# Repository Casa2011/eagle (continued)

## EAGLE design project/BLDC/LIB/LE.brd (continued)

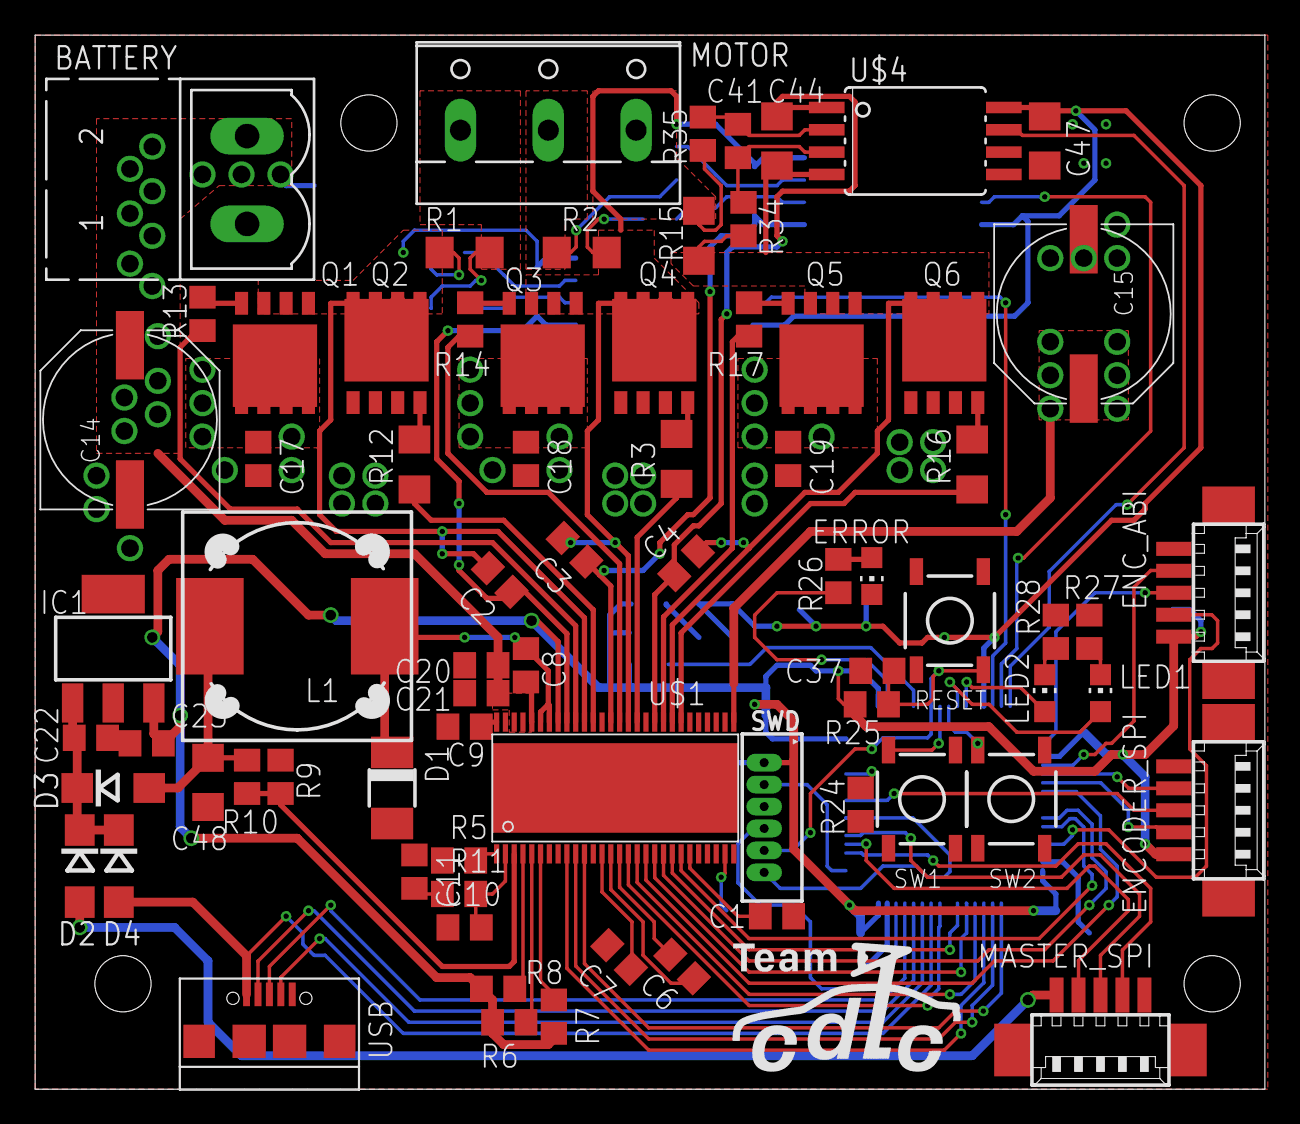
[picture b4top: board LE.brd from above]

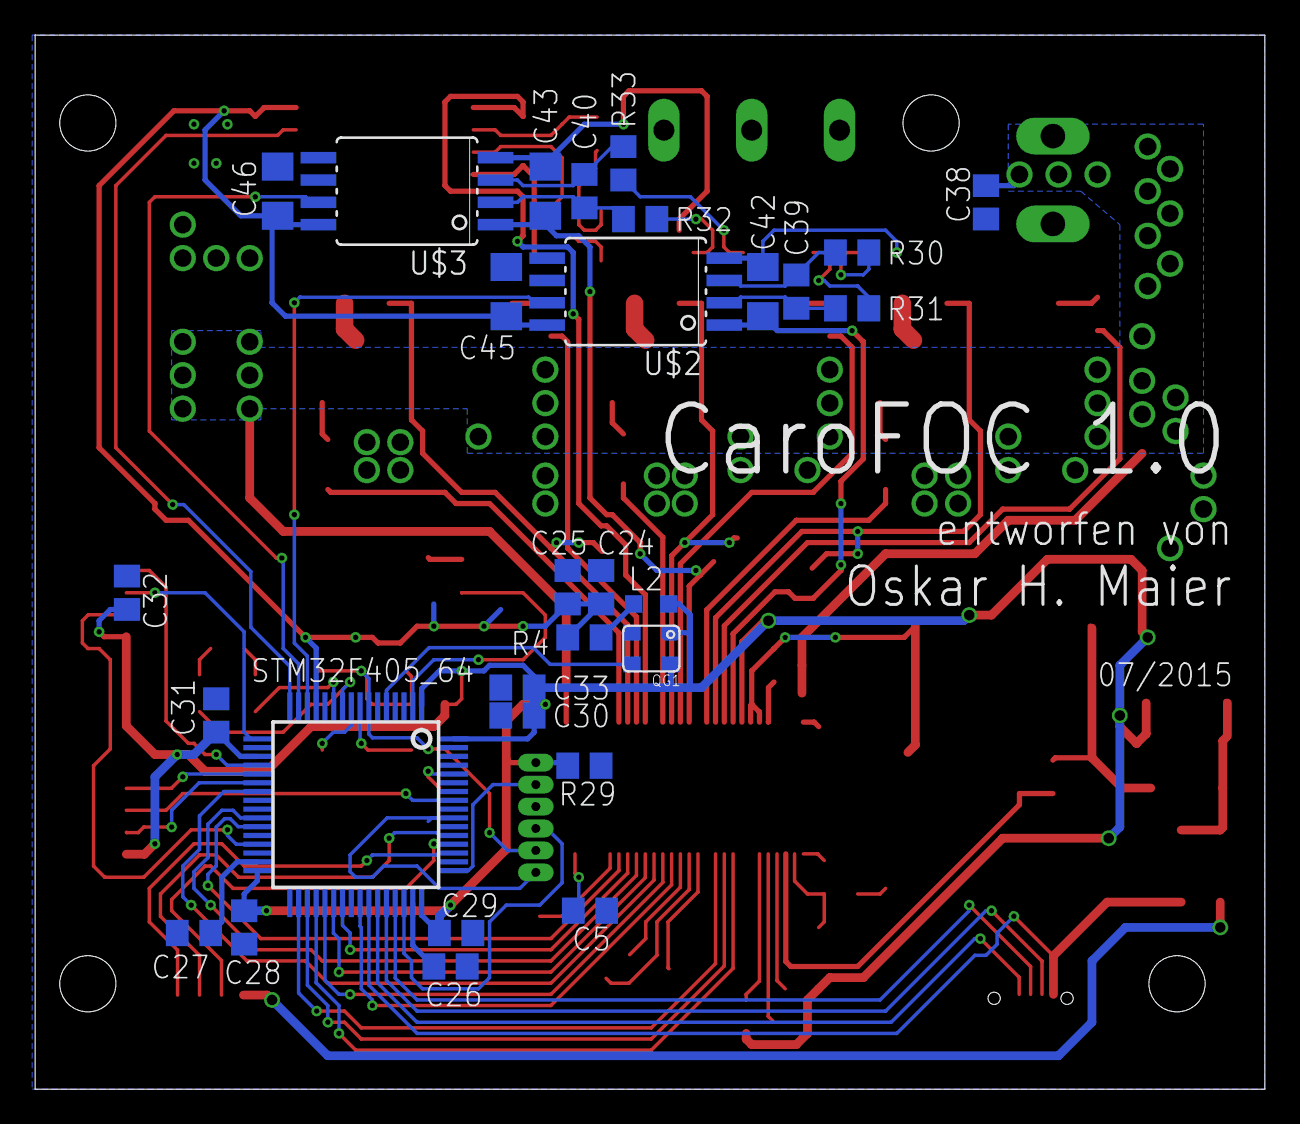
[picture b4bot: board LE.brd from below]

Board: 2 copper layers, 70.0 x 60.0 mm, 103 parts (29 on the bottom side), 92 nets.

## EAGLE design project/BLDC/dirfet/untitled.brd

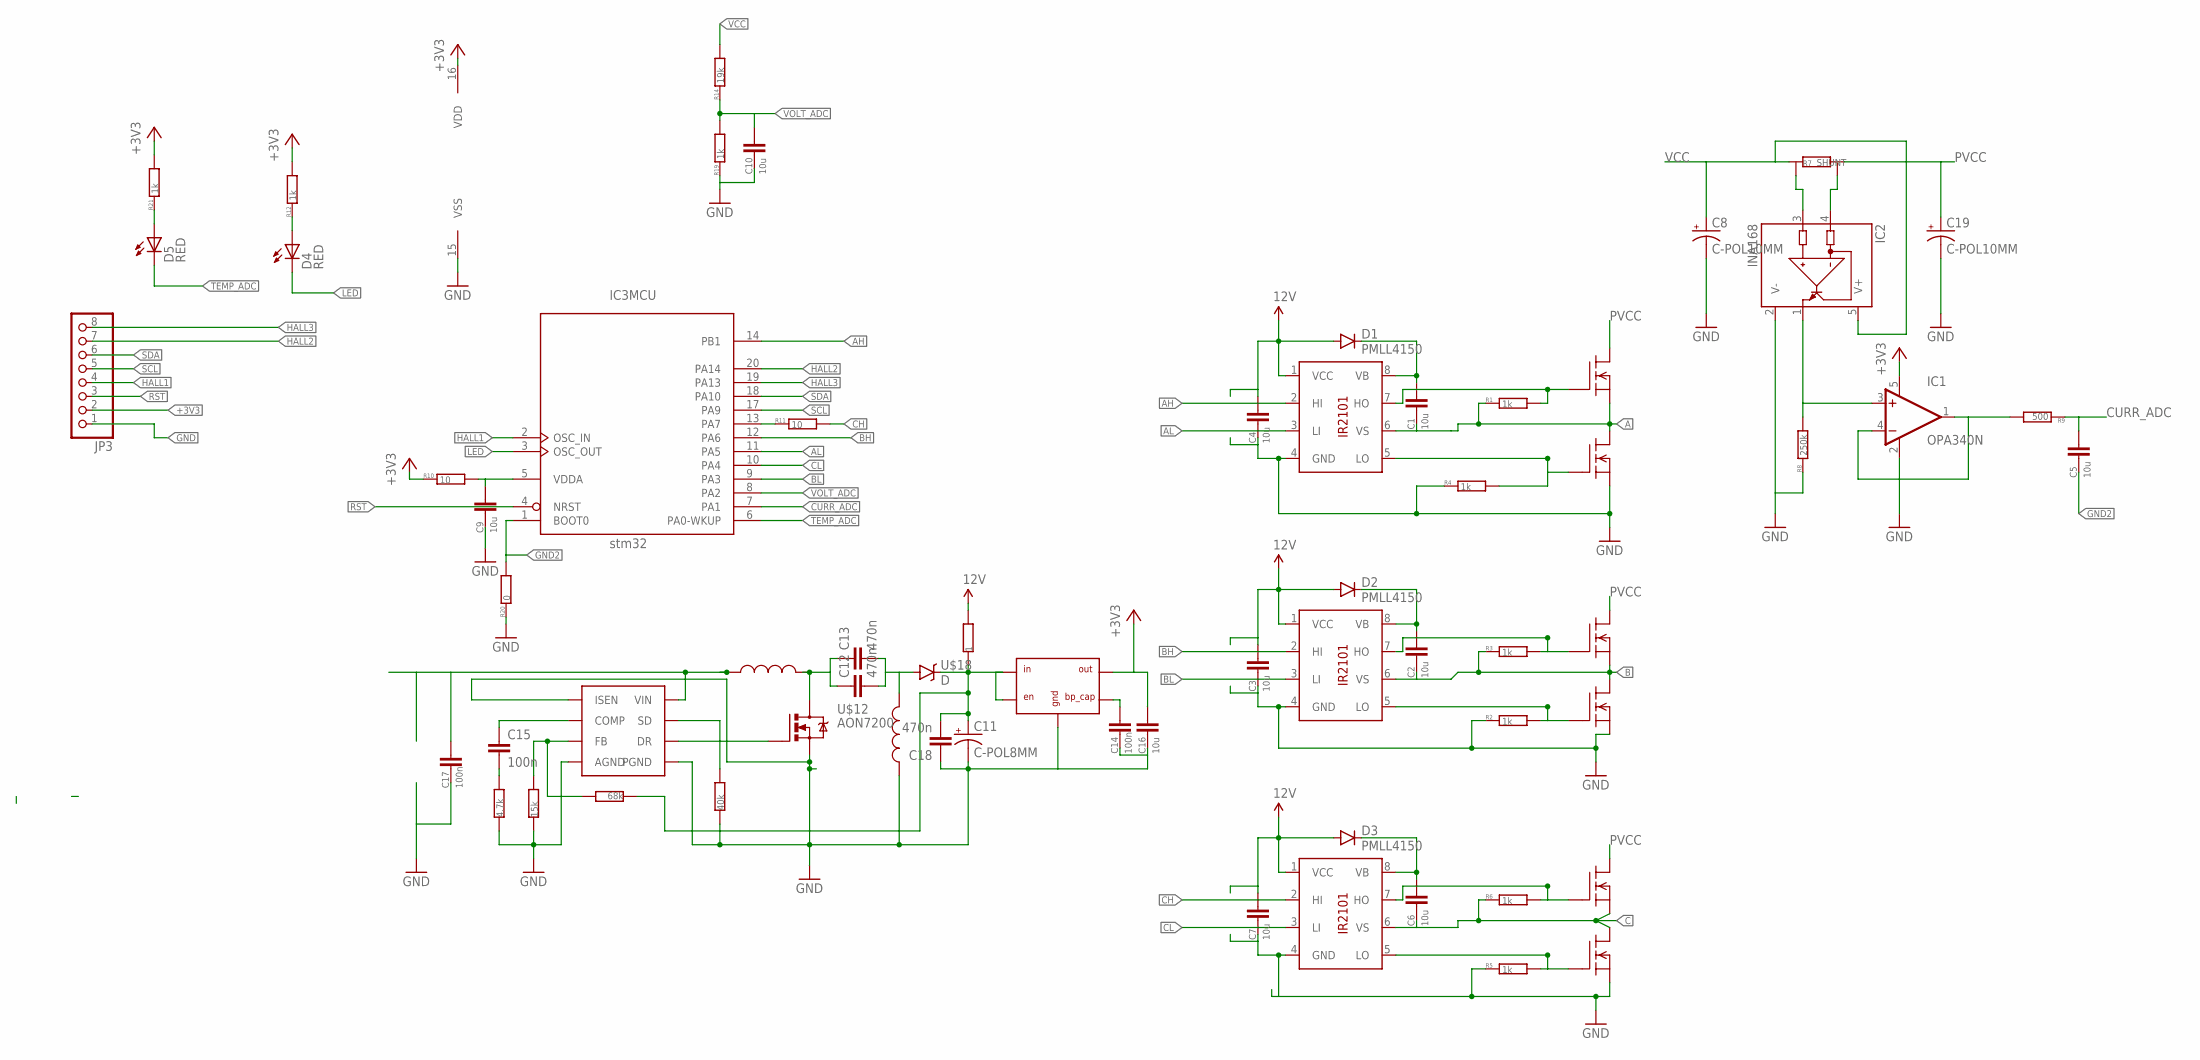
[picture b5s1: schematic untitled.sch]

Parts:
C1, C2, C3, C4, C6, C7, C9, C10, C16: 10u; C0805
C5: 10u; C0603
C8, C19: C-POL10MM; PCAP10
C11: C-POL8MM; PCAP8
C12, C13: 470n; C1206
C14: 100n; C0805
C15: 100n; C0603
C17: 100n; C1206
C18: 470n; C0805
D1, D2, D3: PMLL4150; SOD80C
D4, D5: RED; 0603-LED
IC1: OPA340N; SOT23-5
IC2: INA168; SOT23-5
IC3: stm32; TSSOP20-I
IC4: LM258DG; SOT23-5L
JP3: PINHD-1X8; 1X08
Q1, Q2, Q3, Q4, Q5, Q6: DFET; DIRECT-FET
R1, R2, R3, R4, R5, R6, R12, R21: 1k; 0603
R7: SHUNT
R8: 250k; 0603
R9: 500; R0805
R10: 10; 0603
R11: 10; R0805
R13: 1; R0805
R14: 19k; R1206
R15: 40k; 0603
R16: 4.7k; 0603
R17: 15k; 0603
R18: 68k; R0805
R19: 1k; R0805
R20: 0; R0805
U$1, U$2, U$3: IR2101; SO08
U$4, U$5: INDUCTOR; 8MM_INDURCOR
U$8: LM3488; S-PDSO-G8
U$12: AON7200; DFN3X3
U$18: D; SMA-DIODE

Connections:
12V: C3.1, C4.1, C7.1, D1.A, D2.A, D3.A, R13.2, U$1.1 (VCC), U$2.1 (VCC), U$3.1 (VCC)
12VIN: C11.P$1 (+), C18.2, IC4.1 (IN), IC4.3 (EN), R13.1, R18.1, U$18.C
+3V3: C16.1, IC1.5 (V+), IC3.16 (VDD), IC4.5 (OUT), JP3.2, R10.1, R12.2, R21.2
A: C1.2, Q1.S, Q1.S1 (S), Q2.D, Q2.D1 (D), R1.1, U$1.6 (VS)
AH: IC3.14 (PB1), U$1.2 (HI)
AL: IC3.11 (PA5), U$1.3 (LI)
B: C2.2, Q3.S, Q3.S1 (S), Q4.D, Q4.D1 (D), R3.1, U$2.6 (VS)
BH: IC3.12 (PA6), U$2.2 (HI)
BL: IC3.9 (PA3), U$2.3 (LI)
C: C6.2, Q5.S, Q5.S1 (S), Q6.D, Q6.D1 (D), R6.1, U$3.6 (VS)
CH: R11.2, U$3.2 (HI)
CL: IC3.10 (PA4), U$3.3 (LI)
CURR_ADC: C5.1, IC3.7 (PA1), R9.1
GND: C3.2, C4.2, C7.2, C8.P$2 (-), C9.2, C10.2, C11.P$2 (-), C14.2, C16.2, C17.2, C18.1, C19.P$2 (-), IC1.2 (V-), IC2.2 (V-), IC3.15 (VSS), IC4.2 (GND), JP3.1, Q2.S, Q2.S1 (S), Q4.S, Q4.S1 (S), Q6.S, Q6.S1 (S), R2.1, R4.1, R5.1, R8.1, R15.1, R16.1, R17.1, R19.1, R20.1, U$1.4 (GND), U$2.4 (GND), U$3.4 (GND), U$4.P$1, U$8.1 (ISEN), U$8.4 (AGND), U$8.5 (PGND), U$12.S:1 (S), U$12.S:2 (S), U$12.S:3 (S)
GND2: C5.2, IC3.1 (BOOT0), R20.2
HALL1: IC3.2 (OSC_IN), JP3.4
HALL2: IC3.20 (PA14), JP3.7
HALL3: IC3.19 (PA13), JP3.8
LED: D4.C, IC3.3 (OSC_OUT)
unnamed: Q3.GATE (G), R3.2, U$2.7 (HO)
unnamed: C2.1, D2.C, U$2.8 (VB)
unnamed: Q4.GATE (G), R2.2, U$2.5 (LO)
unnamed: Q1.GATE (G), R1.2, U$1.7 (HO)
unnamed: C1.1, D1.C, U$1.8 (VB)
unnamed: Q5.GATE (G), R6.2, U$3.7 (HO)
unnamed: C6.1, D3.C, U$3.8 (VB)
unnamed: Q2.GATE (G), R4.2, U$1.5 (LO)
unnamed: Q6.GATE (G), R5.2, U$3.5 (LO)
unnamed: IC2.3 (IN+), R7.P$3
unnamed: IC2.4 (IN-), R7.P$4
unnamed: C14.1, IC4.4 (CAP)
unnamed: IC3.13 (PA7), R11.1
unnamed: IC1.3 (+IN), IC2.1 (OUT), R8.2
unnamed: IC1.1 (OUT), IC1.4 (-IN), R9.2
unnamed: C9.1, IC3.5 (VDDA), R10.2
unnamed: D4.A, R12.1
unnamed: D5.A, R21.1
unnamed: R15.2, U$8.7 (SD)
unnamed: U$8.6 (DR), U$12.G
unnamed: C12.1, C13.1, U$5.P$2, U$12.D, U$12.D:1 (D), U$12.D:2 (D), U$12.D:3 (D), U$12.D:4 (D), U$12.D:5 (D), U$12.D:6 (D)
unnamed: C12.2, C13.2, U$4.P$2, U$18.A
unnamed: C15.1, U$8.2 (COMP)
unnamed: C15.2, R16.2
unnamed: R17.2, R18.2, U$8.3 (FB)
PVCC: C19.P$1 (+), Q1.D, Q1.D1 (D), Q3.D, Q3.D1 (D), Q5.D, Q5.D1 (D), R7.P$2 (2)
RST: IC3.4 (NRST), JP3.3
SCL: IC3.17 (PA9), JP3.5
SDA: IC3.18 (PA10), JP3.6
TEMP_ADC: D5.C, IC3.6 (PA0-WKUP)
VCC: C8.P$1 (+), C17.1, IC2.5 (V+), R7.P$1 (1), R14.2, U$5.P$1, U$8.8 (VIN)
VOLT_ADC: C10.1, IC3.8 (PA2), R14.1, R19.2

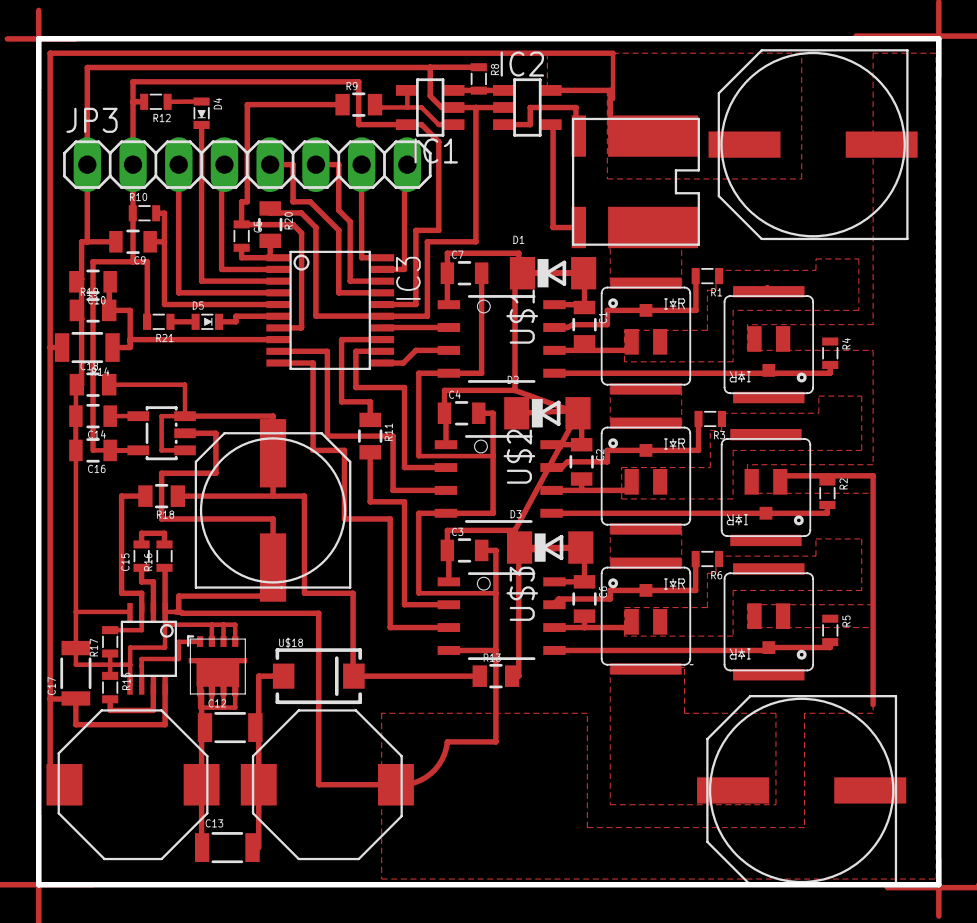
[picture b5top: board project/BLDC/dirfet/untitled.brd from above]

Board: 2 copper layers, 50.0 x 47.0 mm, 64 parts (0 on the bottom side), 51 nets.

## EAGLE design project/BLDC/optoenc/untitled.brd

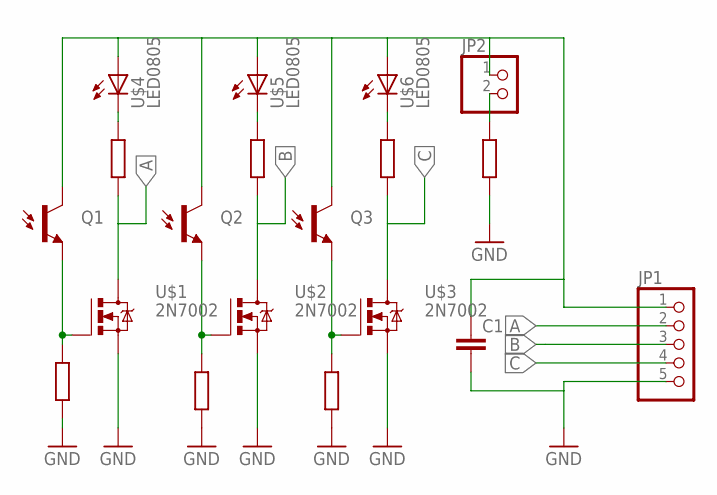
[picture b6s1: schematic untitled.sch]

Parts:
C1: CC0805; C0805
JP1: PINHD-1X5; 1X05
JP2: PINHD-1X2; 1X02
Q1, Q2, Q3: PHOTOTRANSISTORPT17-21C-L41-TR8; PT17-21C-L41-TR8
R1, R4, R5, R6, R7, R8, R9: R0805
U$1, U$2, U$3: 2N7002; SOT23
U$4, U$5, U$6: LED0805; 0805-LED

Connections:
A: JP1.2, R7.1, U$1.3 (D)
B: JP1.3, R8.1, U$2.3 (D)
C: JP1.4, R9.1, U$3.3 (D)
GND: C1.2, JP1.5, R1.1, R4.1, R5.1, R6.1, U$1.2 (S), U$2.2 (S), U$3.2 (S)
unnamed: C1.1, JP1.1, JP2.1, Q1.C, Q2.C, Q3.C, U$4.A, U$5.A, U$6.A
unnamed: Q1.E, R4.2, U$1.1 (G)
unnamed: Q2.E, R5.2, U$2.1 (G)
unnamed: Q3.E, R6.2, U$3.1 (G)
unnamed: JP2.2, R1.2
unnamed: R7.2, U$4.C
unnamed: R8.2, U$5.C
unnamed: R9.2, U$6.C

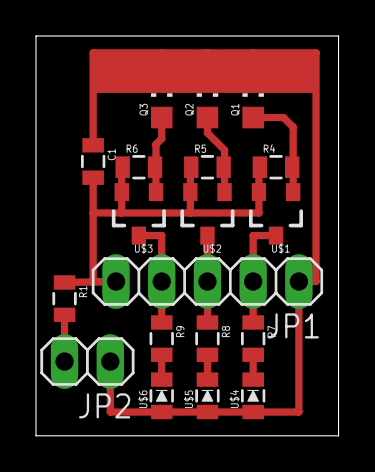
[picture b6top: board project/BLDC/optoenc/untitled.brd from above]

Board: 2 copper layers, 16.8 x 22.2 mm, 19 parts (0 on the bottom side), 12 nets.

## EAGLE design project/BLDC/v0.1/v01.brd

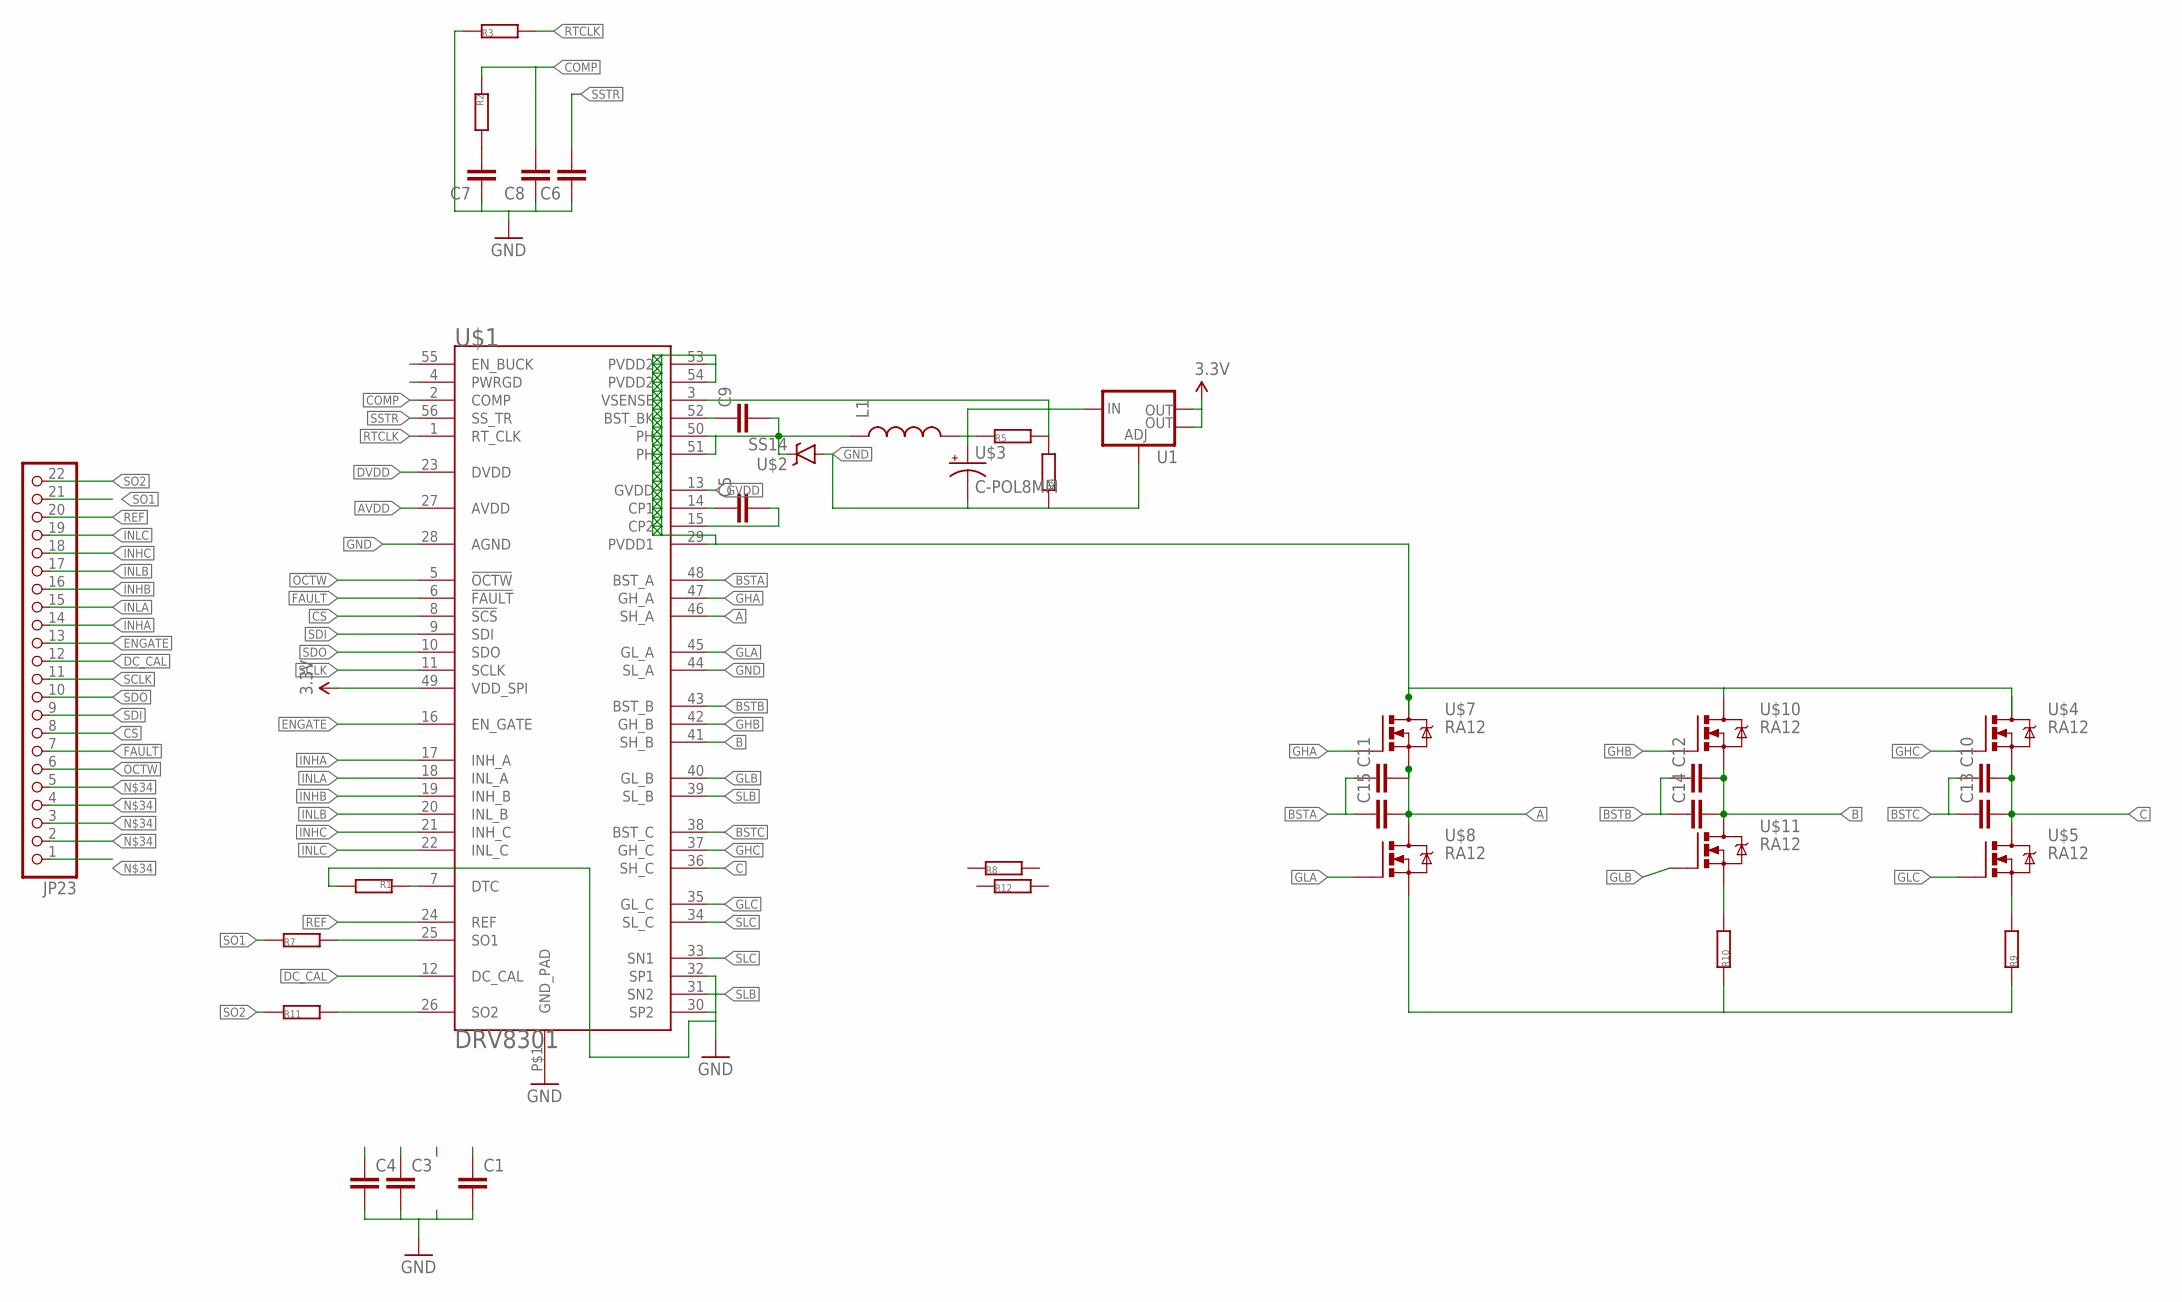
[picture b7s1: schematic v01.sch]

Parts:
C1, C3, C4, C6, C7, C8, C10, C11, C12, C13, C14, C15: CC0805; C0805
C5, C9: CC0603; C0603
JP23: PINHD-1X22; 1X22
L1: INDUCTORDR1030; DR1030
R1, R2, R3, R4, R5, R7, R11: R0603; 0603
R8, R12: R1206
R9, R10: R2512
U1: V_REG_LM1117SOT223; SOT223
U$1: DRV8301; HTSSOP56DCA
U$2: SS14; SMA-DIODE
U$3: C-POL8MM; PCAP8
U$4, U$5, U$7, U$8, U$10, U$11: RA12; POWERPAK_SO8

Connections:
3.3V: U1.2 (OUT), U1.4 (OUT), U$1.49 (VDD_SPI)
5V: L1.2, R5.1, U1.3 (IN), U$3.P$1 (+)
!CS: JP23.8, U$1.8 (!SCS)
!FAULT: JP23.7, U$1.6 (!FAULT)
!OCTW: JP23.6, U$1.5 (!OCTW)
A: C11.2, C15.2, U$1.46 (SH_A), U$7.1 (S), U$7.2 (S), U$7.3 (S), U$8.5 (D), U$8.6 (D), U$8.7 (D), U$8.8 (D)
AVDD: C4.1, U$1.27 (AVDD)
B: C12.2, C14.2, U$1.41 (SH_B), U$10.1 (S), U$10.2 (S), U$10.3 (S), U$11.5 (D), U$11.6 (D), U$11.7 (D), U$11.8 (D)
BSTA: C11.1, C15.1, U$1.48 (BST_A)
BSTB: C12.1, C14.1, U$1.43 (BST_B)
BSTC: C10.1, C13.1, U$1.38 (BST_C)
C: C10.2, C13.2, U$1.36 (SH_C), U$4.1 (S), U$4.2 (S), U$4.3 (S), U$5.5 (D), U$5.6 (D), U$5.7 (D), U$5.8 (D)
COMP: C8.2, R2.1, U$1.2 (COMP)
DC_CAL: JP23.12, U$1.12 (DC_CAL)
DVDD: C3.1, U$1.23 (DVDD)
ENGATE: JP23.13, U$1.16 (EN_GATE)
GHA: U$1.47 (GH_A), U$7.4 (G)
GHB: U$1.42 (GH_B), U$10.4 (G)
GHC: U$1.37 (GH_C), U$4.4 (G)
GLA: U$1.45 (GL_A), U$8.4 (G)
GLB: U$1.40 (GL_B), U$11.4 (G)
GLC: U$1.35 (GL_C), U$5.4 (G)
GND: C1.2, C3.2, C4.2, C6.1, C7.1, C8.1, R1.2, R3.1, R4.1, R9.P$1 (1), R10.P$1 (1), U1.1 (ADJ), U$1.28 (AGND), U$1.30 (SP2), U$1.32 (SP1), U$1.44 (SL_A), U$1.P$1 (GND_PAD), U$2.A, U$3.P$2 (-), U$8.1 (S), U$8.2 (S), U$8.3 (S)
GVDD: C1.1, U$1.13 (GVDD)
INHA: JP23.14, U$1.17 (INH_A)
INHB: JP23.16, U$1.19 (INH_B)
INHC: JP23.18, U$1.21 (INH_C)
INLA: JP23.15, U$1.18 (INL_A)
INLB: JP23.17, U$1.20 (INL_B)
INLC: JP23.19, U$1.22 (INL_C)
unnamed: C9.2, L1.1, U$1.50 (PH), U$1.51 (PH), U$2.C
unnamed: R7.2, U$1.25 (SO1)
unnamed: R11.2, U$1.26 (SO2)
unnamed: C5.1, U$1.14 (CP1)
unnamed: C5.2, U$1.15 (CP2)
unnamed: R1.1, U$1.7 (DTC)
unnamed: C7.2, R2.2
unnamed: C9.1, U$1.52 (BST_BK)
unnamed: R4.2, R5.2, U$1.3 (VSENSE)
unnamed: JP23.1, JP23.2, JP23.3, JP23.4, JP23.5
REF: JP23.20, U$1.24 (REF)
RTCLK: R3.2, U$1.1 (RT_CLK)
SCLK: JP23.11, U$1.11 (SCLK)
SDI: JP23.9, U$1.9 (SDI)
SDO: JP23.10, U$1.10 (SDO)
SLB: R10.P$2 (2), U$1.31 (SN2), U$1.39 (SL_B), U$11.1 (S), U$11.2 (S), U$11.3 (S)
SLC: R9.P$2 (2), U$1.33 (SN1), U$1.34 (SL_C), U$5.1 (S), U$5.2 (S), U$5.3 (S)
SO1: JP23.21, R7.1
SO2: JP23.22, R11.1
SSTR: C6.2, U$1.56 (SS_TR)
VCC: U$1.29 (PVDD1), U$1.53 (PVDD2), U$1.54 (PVDD2), U$4.5 (D), U$4.6 (D), U$4.7 (D), U$4.8 (D), U$7.5 (D), U$7.6 (D), U$7.7 (D), U$7.8 (D), U$10.5 (D), U$10.6 (D), U$10.7 (D), U$10.8 (D)

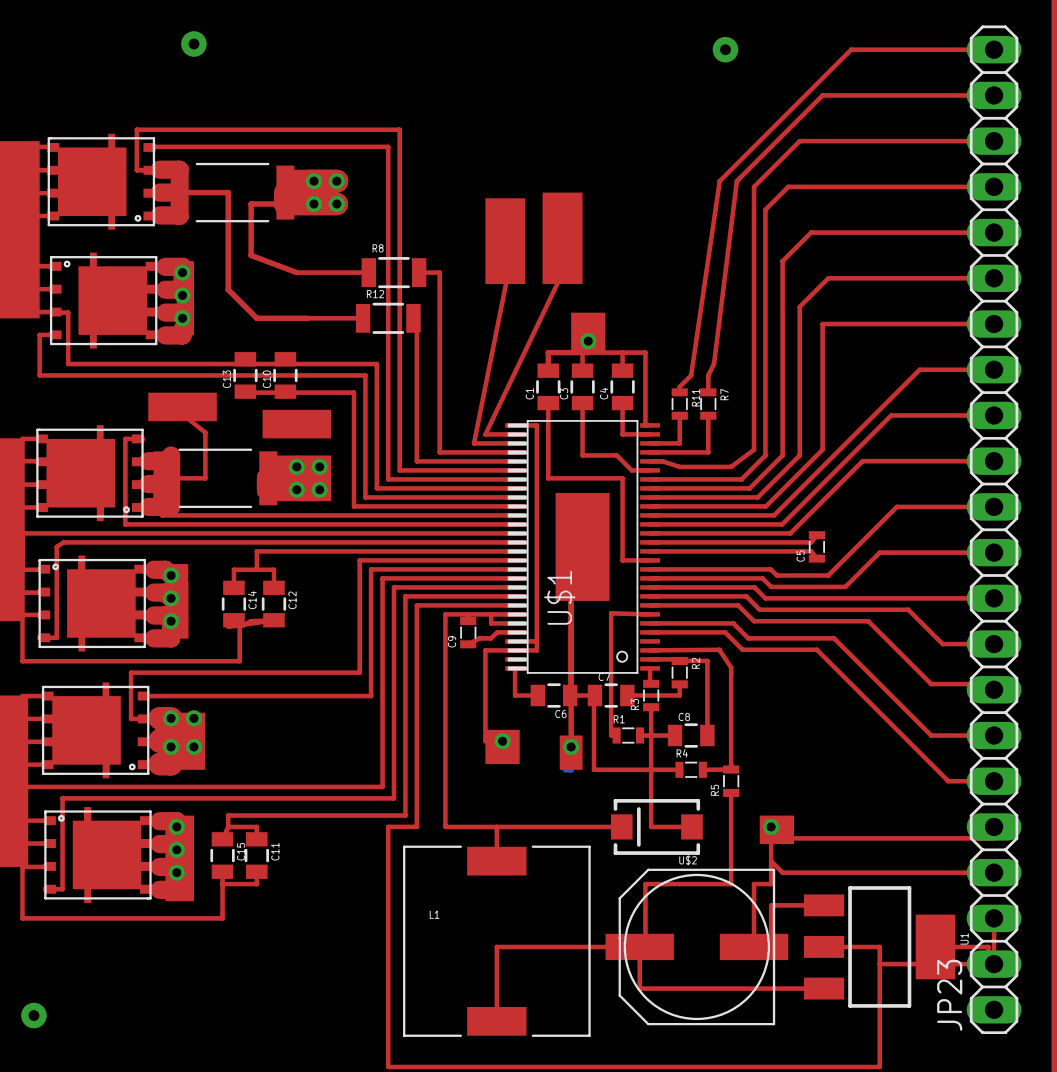
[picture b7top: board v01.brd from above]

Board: 2 copper layers, 37 parts (0 on the bottom side), 51 nets.
